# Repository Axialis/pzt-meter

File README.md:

# PZT-meter
PZT impedance measuring device

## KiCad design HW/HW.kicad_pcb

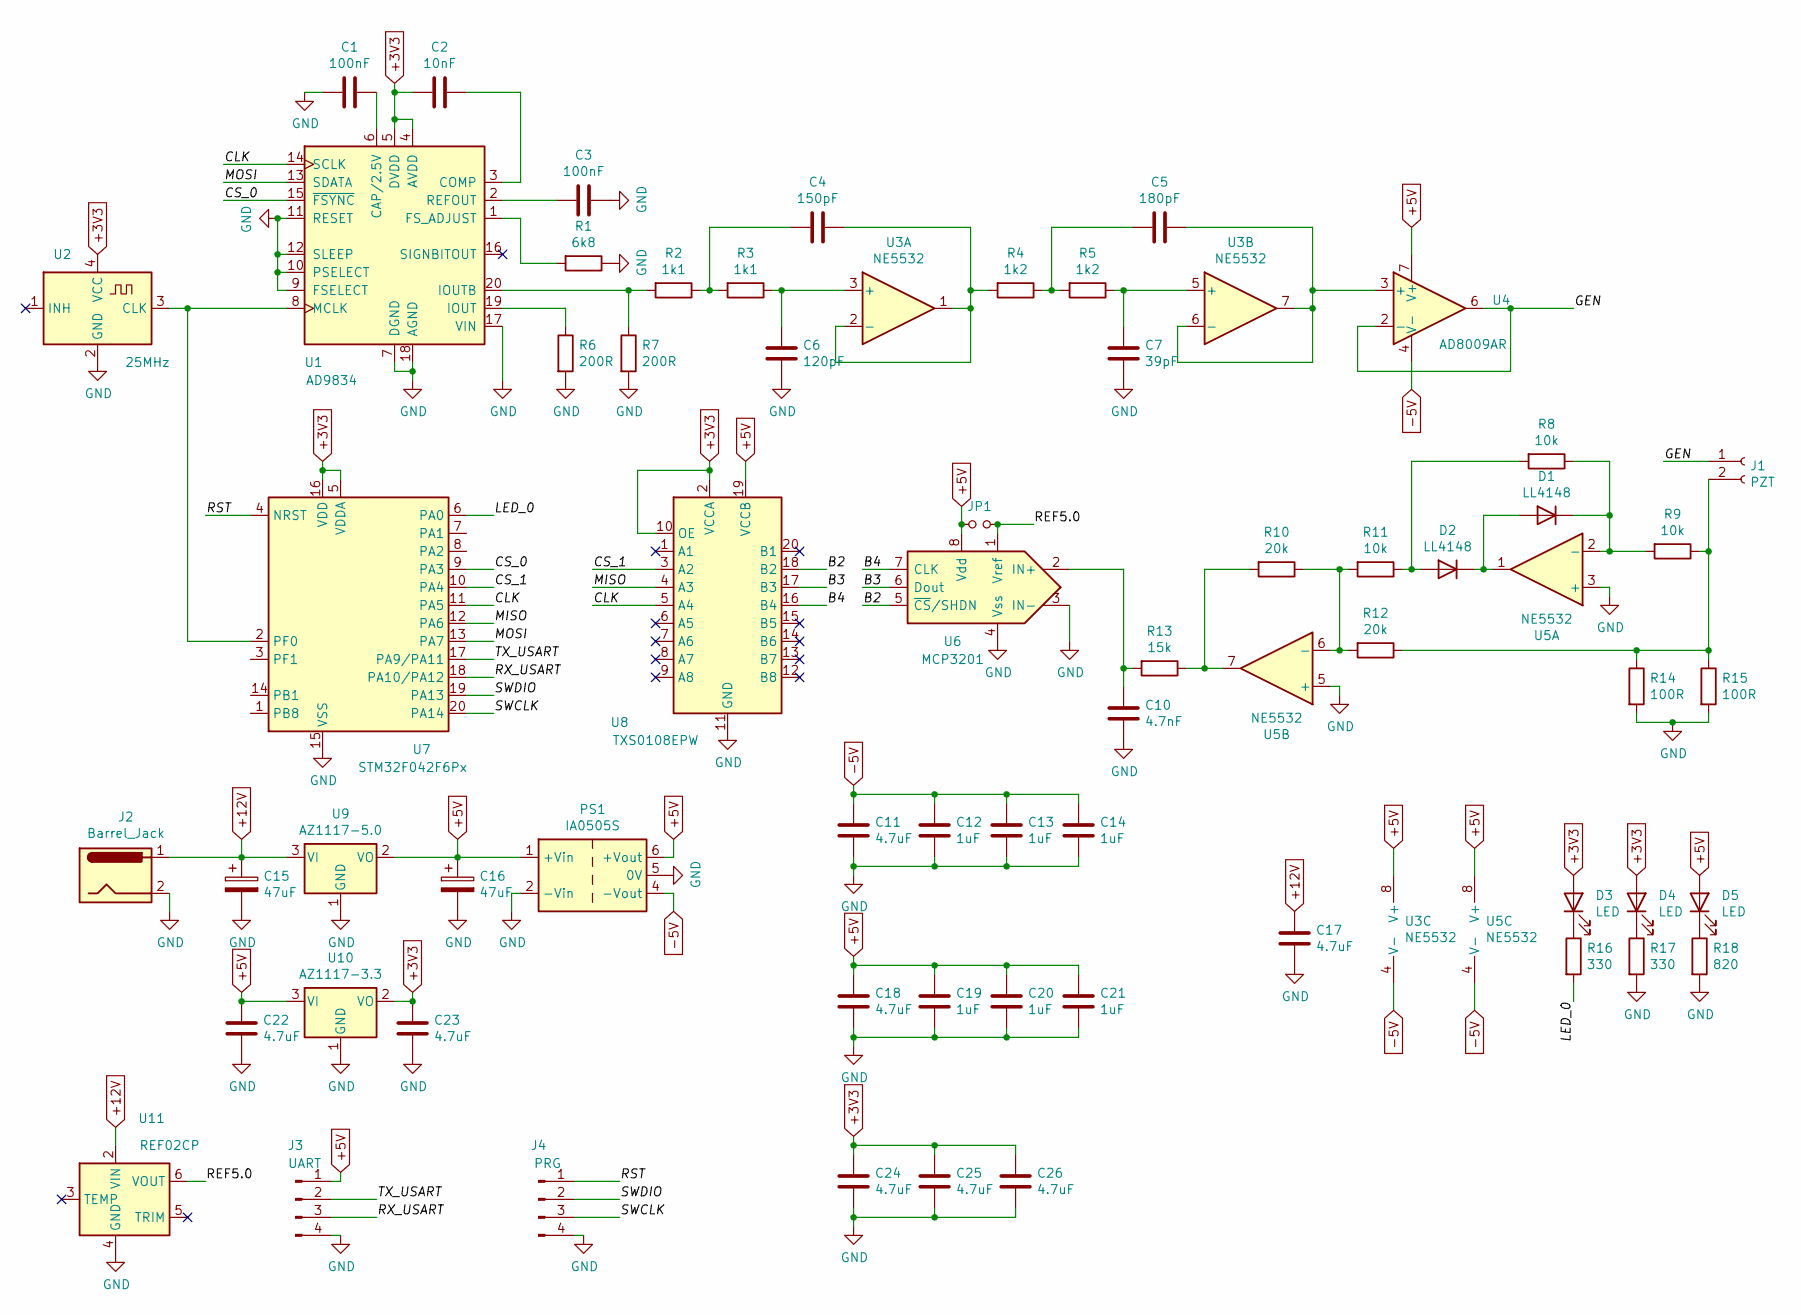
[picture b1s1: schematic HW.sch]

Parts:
C1, C3: 100nF; C_0603_1608Metric_Pad1.08x0.95mm_HandSolder
C2: 10nF; C_0603_1608Metric_Pad1.08x0.95mm_HandSolder
C4: 150pF; C_0603_1608Metric_Pad1.08x0.95mm_HandSolder
C5: 180pF; C_0603_1608Metric_Pad1.08x0.95mm_HandSolder
C6: 120pF; C_0603_1608Metric_Pad1.08x0.95mm_HandSolder
C7: 39pF; C_0603_1608Metric_Pad1.08x0.95mm_HandSolder
C10: 4.7nF; C_0603_1608Metric_Pad1.08x0.95mm_HandSolder
C11, C17, C18, C22, C23, C24, C25, C26: 4.7uF; C_0603_1608Metric_Pad1.08x0.95mm_HandSolder
C12, C13, C14, C19, C20, C21: 1uF; C_0603_1608Metric_Pad1.08x0.95mm_HandSolder
C15, C16: 47uF; C_Elec_6.3x5.4
D1, D2: LL4148; D_SOD-123
D3, D4, D5: LED; LED_0603_1608Metric_Pad1.05x0.95mm_HandSolder
J1: PZT; SMA_Amphenol_132289_EdgeMount
J2: Barrel_Jack; BarrelJack_Horizontal
J3: UART; PinHeader_1x04_P2.54mm_Vertical
J4: PRG; PinHeader_1x04_P2.54mm_Vertical
JP1: Jumper_NO_Small; SolderJumper-2_P1.3mm_Open_RoundedPad1.0x1.5mm
PS1: IA0505S; Converter_DCDC_XP_POWER-IAxxxxS_THT
R1: 6k8; R_0603_1608Metric_Pad0.98x0.95mm_HandSolder
R2, R3: 1k1; R_0603_1608Metric_Pad0.98x0.95mm_HandSolder
R4, R5: 1k2; R_0603_1608Metric_Pad0.98x0.95mm_HandSolder
R6, R7: 200R; R_0603_1608Metric_Pad0.98x0.95mm_HandSolder
R8, R9, R11: 10k; R_0603_1608Metric_Pad0.98x0.95mm_HandSolder
R10, R12: 20k; R_0603_1608Metric_Pad0.98x0.95mm_HandSolder
R13: 15k; R_0603_1608Metric_Pad0.98x0.95mm_HandSolder
R14, R15: 100R; R_0805_2012Metric_Pad1.20x1.40mm_HandSolder
R16, R17: 330; R_0603_1608Metric_Pad0.98x0.95mm_HandSolder
R18: 820; R_0603_1608Metric_Pad0.98x0.95mm_HandSolder
U1: AD9834; TSSOP-20_4.4x6.5mm_P0.65mm
U2: 25MHz; Oscillator_SMD_SeikoEpson_SG8002CA-4Pin_7.0x5.0mm
U3, U5: NE5532; SOIC-8_3.9x4.9mm_P1.27mm
U4: AD8009AR; SOIC-8_3.9x4.9mm_P1.27mm
U6: MCP3201; SOIC-8_3.9x4.9mm_P1.27mm
U7: STM32F042F6Px; TSSOP-20_4.4x6.5mm_P0.65mm
U8: TXS0108EPW; TSSOP-20_4.4x6.5mm_P0.65mm
U9: AZ1117-5.0; SOT-223-3_TabPin2
U10: AZ1117-3.3; SOT-223-3_TabPin2
U11: REF02CP; SOIC-8_3.9x4.9mm_P1.27mm

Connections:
+3V3: C2.2, C23.1, C24.1, C25.1, C26.1, D3.2 (A), D4.2 (A), U1.4 (AVDD), U1.5 (DVDD), U2.4 (VCC), U7.5 (VDDA), U7.16 (VDD), U8.2 (VCCA), U8.10 (OE), U10.2 (VO)
+5V: C16.1, C18.1, C19.1, C20.1, C21.1, C22.1, D5.2 (A), J3.1, JP1.1, PS1.1 (+Vin), PS1.6 (+Vout), U3.8 (V+), U4.7 (V+), U5.8 (V+), U6.8 (Vdd), U8.19 (VCCB), U9.2 (VO), U10.3 (VI)
+12V: C15.1, C17.1, J2.1, U9.3 (VI), U11.2 (VIN)
-5V: C11.1, C12.1, C13.1, C14.1, PS1.4 (-Vout), U3.4 (V-), U4.4 (V-), U5.4 (V-)
/B2: U6.5 (~CS~/SHDN), U8.18 (B2)
/B3: U6.6 (Dout), U8.17 (B3)
/B4: U6.7 (CLK), U8.16 (B4)
/CLK: U1.14 (SCLK), U7.11 (PA5), U8.5 (A4)
/CS_0: U1.15 (~FSYNC), U7.9 (PA3)
/CS_1: U7.10 (PA4), U8.3 (A2)
/GEN: J1.1, U4.2 (-), U4.6
/LED_0: R16.2, U7.6 (PA0)
/MISO: U7.12 (PA6), U8.4 (A3)
/MOSI: U1.13 (SDATA), U7.13 (PA7)
/REF5.0: JP1.2, U6.1 (Vref), U11.6 (VOUT)
/RST: J4.1, U7.4 (NRST)
/RX_USART: J3.3, U7.18 (PA10/PA12)
/SWCLK: J4.3, U7.20 (PA14)
/SWDIO: J4.2, U7.19 (PA13)
/TX_USART: J3.2, U7.17 (PA9/PA11)
GND: C1.2, C3.1, C6.2, C7.2, C10.2, C11.2, C12.2, C13.2, C14.2, C15.2, C16.2, C17.2, C18.2, C19.2, C20.2, C21.2, C22.2, C23.2, C24.2, C25.2, C26.2, J2.2, J3.4, J4.4, PS1.2 (-Vin), PS1.5 (0V), R1.1, R6.2, R7.2, R14.2, R15.2, R17.2, R18.2, U1.7 (DGND), U1.9 (FSELECT), U1.10 (PSELECT), U1.11 (RESET), U1.12 (SLEEP), U1.17 (VIN), U1.18 (AGND), U2.2 (GND), U5.3 (+), U5.5 (+), U6.3 (IN-), U6.4 (Vss), U7.15 (VSS), U8.11 (GND), U9.1 (GND), U10.1 (GND), U11.4 (GND)
unnamed: C1.1, U1.6 (CAP/2.5V)
unnamed: C2.1, U1.3 (COMP)
unnamed: C3.2, U1.2 (REFOUT)
unnamed: C4.1, R4.2, U3.1, U3.2 (-)
unnamed: C4.2, R2.1, R3.2
unnamed: C5.1, U3.6 (-), U3.7, U4.3 (+)
unnamed: C5.2, R4.1, R5.2
unnamed: C6.1, R3.1, U3.3 (+)
unnamed: C7.1, R5.1, U3.5 (+)
unnamed: C10.1, R13.2, U6.2 (IN+)
unnamed: D1.1 (K), R8.1, R9.2, U5.2 (-)
unnamed: D1.2 (A), D2.1 (K), U5.1
unnamed: D2.2 (A), R8.2, R11.1
unnamed: D3.1 (K), R16.1
unnamed: D4.1 (K), R17.1
unnamed: D5.1 (K), R18.1
unnamed: J1.2, R9.1, R12.1, R14.1, R15.1
unnamed: R1.2, U1.1 (FS_ADJUST)
unnamed: R2.2, R7.1, U1.20 (IOUTB)
unnamed: R6.1, U1.19 (IOUT)
unnamed: R10.1, R11.2, R12.2, U5.6 (-)
unnamed: R10.2, R13.1, U5.7
unnamed: U1.8 (MCLK), U2.3 (CLK), U7.2 (PF0)

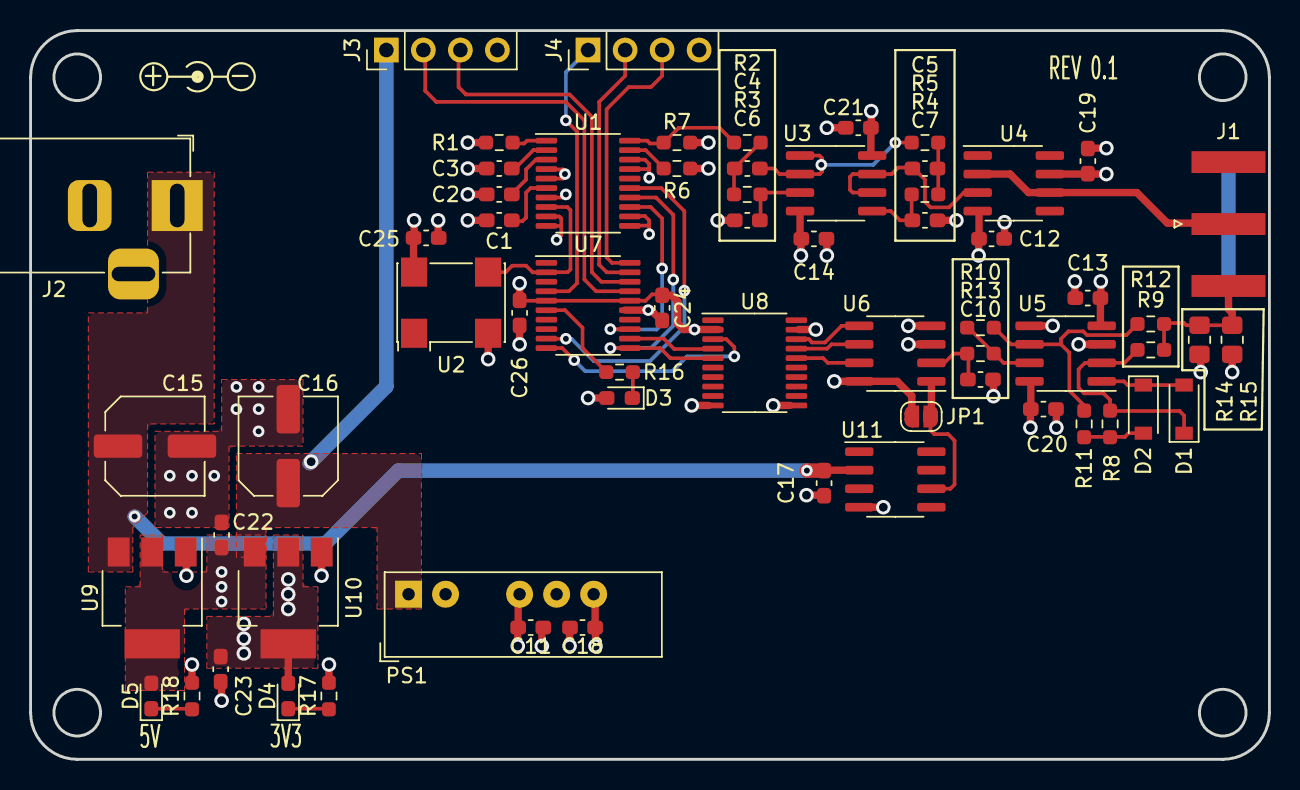
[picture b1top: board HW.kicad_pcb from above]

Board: 4 copper layers, 85.0 x 50.0 mm, 64 parts (0 on the bottom side), 44 nets.

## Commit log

2022-01-13 feat: schematic
2022-01-20 add: gerber
